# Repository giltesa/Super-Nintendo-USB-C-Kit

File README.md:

# Super Nintendo: USB-C Kit

The **Super Nintendo: USB-C Kit** is a board that allows to replace the original power connector for a modern and standard USB-C.

**If your original connector is too old or damaged** and you need a new one, or **if you would like to power up your Super Nintendo with a standard USB-C charger**, such as the charger for your **Nintendo Switch**, phone, or laptop, you can do so with this kit.

Moreover, with this board, **you can remove the original, old, and inefficient power converter**. Since the console operates at 5V, you only need the power from USB-C and a regular charger.

## Would you like it?

[**Super Nintendo USB-C Kit (EN)**](https://shop.giltesa.com/product/super-nintendo-usb-c-kit/)

## License

This project is licensed under a **Creative Commons** license:
**[Attribution-NonCommercial-ShareAlike 4.0 International (CC BY-NC-SA 4.0) ](https://creativecommons.org/licenses/by-nc-sa/4.0/)**

Check the [LICENSE.md](LICENSE.md) for more information.

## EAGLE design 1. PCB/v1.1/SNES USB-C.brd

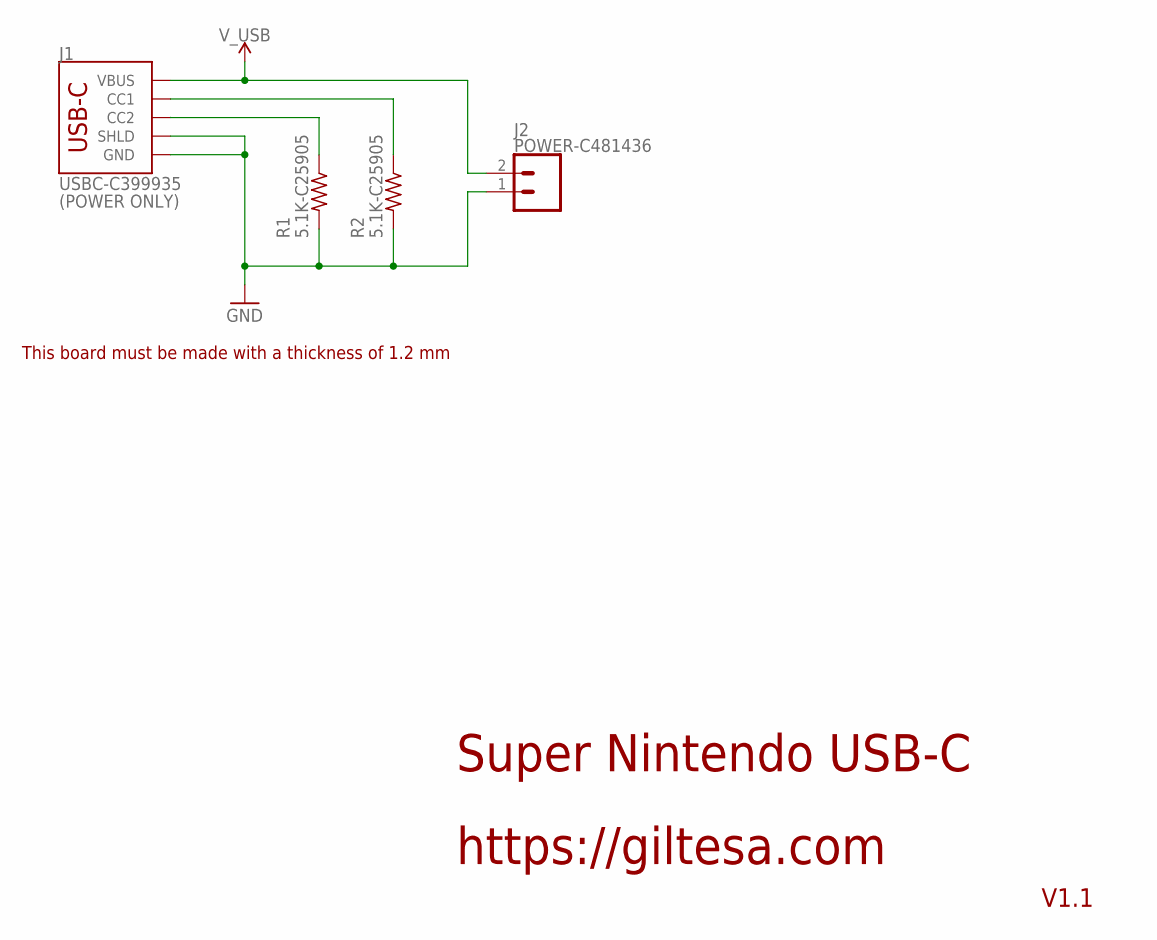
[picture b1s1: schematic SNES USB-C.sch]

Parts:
J1: USBC-C399935; USB-C_6P_SIDE
J2: POWER-C481436; JST-2-1.25MM_RIGHT
R1, R2: 5.1K-C25905; R0402

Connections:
GND: J1.A12-GND (GND), J1.B12-GND (GND), J1.SHLD1 (SHLD), J1.SHLD2 (SHLD), J1.SHLD3 (SHLD), J1.SHLD4 (SHLD), J2.1, R1.2, R2.2
unnamed: J1.B5 (CC2), R1.1
unnamed: J1.A5 (CC1), R2.1
V_USB: J1.A9-VBUS (VBUS), J1.B9-VBUS (VBUS), J2.2

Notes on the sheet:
Super Nintendo USB-C
https://giltesa.com
V1.1
This board must be made with a thickness of 1.2 mm
(POWER ONLY)

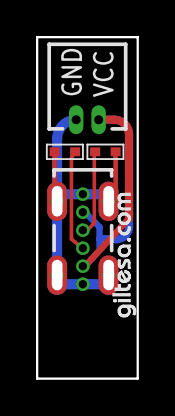
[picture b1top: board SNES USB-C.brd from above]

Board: 2 copper layers, 5.1 x 18.5 mm, 5 parts (0 on the bottom side), 4 nets.

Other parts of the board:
U$11: GILTESA.COM_MASK_7MM

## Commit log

2023-10-26 no message
2024-10-10 v1.0
2024-10-10 v1.1

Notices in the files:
parts and their libraries:
SparkFun: Licensing: CC v3.0 Share-Alike You are welcome to use this library for commercial purposes.
SparkFun-PowerSymbols: Licensing: Creative Commons ShareAlike 4.0 International - https://creativecommons.org/licenses/by-sa/4.0
